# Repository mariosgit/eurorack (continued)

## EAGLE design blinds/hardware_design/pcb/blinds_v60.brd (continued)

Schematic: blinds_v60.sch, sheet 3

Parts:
C31, C34, C35: 47p; C0603
C37, C38: 560p; C0603
IC8, IC9: OPA4171; TSSOP14
IC10: V2164SZ; SOIC16N
J7, J8, J9: PJ301_THONKICONN6; WQP_PJ_301M6
LED5: WP7113SRSGW; LED5MM
LED6: WP937EGW; LED3MM
R61: 205.0k; R0603
R62, R66, R69, R71: 100k; R0603
R63, R76, R78, R79, R89: 100.0k; R0603
R64: 10kB; ALPS_POT_VERTICAL_PS
R65: 10kB; ALPS_POT_VERTICAL
R67, R68, R73: 4.30k; R0603
R70: 3.90k; R0603
R72, R77, R81, R85: 1.0M; R0603
R74, R82: 66.50k; R0603
R75, R80: 1.2k; R0603
R83, R90: 33.20k; R0603
R84: 402; R0603
R87, R88: 510; R0603

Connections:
2_TO_3: R82.2; also elsewhere on the board
3_TO_4: IC8.14 (OUT), R68.1; also elsewhere on the board
AREF_+10: R61.2, R63.1, R79.2; also elsewhere on the board
AREF_-10: R76.2, R89.2; also elsewhere on the board
FOO2: IC10.2 (IN), R88.2, R89.1
GAIN_3: C31.1, IC9.1 (OUT), R66.1, R81.2, R83.2, R90.2
GND: C37.2, C38.2, IC8.3 (+IN), IC8.5 (+IN), IC8.12 (+IN), IC9.3 (+IN), IC9.5 (+IN), IC9.12 (+IN), J7.P1 (1), J8.P1 (1), J9.P1 (1), J9.P2 (2), R64.P$3 (A), R72.2, R75.2, R77.2, R80.2; also elsewhere on the board
unnamed: J8.P3 (3), R84.1
unnamed: C37.1, R87.1
unnamed: IC10.15 (IN), R87.2, R90.1
unnamed: IC8.2 (-IN), IC10.13 (OUT), R67.2
unnamed: C34.1, IC8.6 (-IN), R73.1, R74.2, R82.1, R83.1
unnamed: J9.P3 (3), R71.2
unnamed: IC9.13 (-IN), R65.P$1 (E), R69.2
unnamed: IC9.14 (OUT), R62.2, R69.1
unnamed: C31.2, IC9.2 (-IN), R61.1, R62.1, R64.P$1 (E), R65.P$3 (A), R66.2
unnamed: R64.P$2 (S), R76.1
unnamed: IC9.8 (OUT), LED6.K (C)
unnamed: IC9.9 (-IN), LED6.A, R80.1
unnamed: IC8.8 (OUT), LED5.K (C)
unnamed: IC8.9 (-IN), LED5.A, R75.1
unnamed: IC8.13 (-IN), R68.2, R70.1
unnamed: J8.P2 (2), R70.2
unnamed: IC8.1 (OUT), R67.1, R73.2
unnamed: C38.1, R88.1
unnamed: C35.1, IC9.6 (-IN), IC10.4 (OUT), R78.1, R79.1
unnamed: C35.2, IC9.7 (OUT), IC10.3 (CTRL), IC10.14 (CTRL)
unnamed: R65.P$2 (S), R71.1
unnamed: J7.P3 (3), R78.2
unnamed: J7.P2 (2), R63.2
unnamed: IC8.10 (+IN), R77.1, R85.1
unnamed: IC9.10 (+IN), R72.1, R81.1
OUT3: C34.2, IC8.7 (OUT), R74.1, R84.2, R85.2

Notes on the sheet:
cc-by-sa
Channel 3
Émilie Gillet
emilie.o.gillet@gmail.com

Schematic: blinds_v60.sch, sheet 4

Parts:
C39, C40: 560p; C0603
C44, C45, C48: 47p; C0603
IC10: V2164SZ; SOIC16N
IC11, IC12: OPA4171; TSSOP14
J10, J11, J12: PJ301_THONKICONN6; WQP_PJ_301M6
LED7: WP7113SRSGW; LED5MM
LED8: WP937EGW; LED3MM
R91, R103: 33.20k; R0603
R92, R95, R101, R102, R109: 100.0k; R0603
R93, R94: 510; R0603
R96, R104, R110, R115: 1.0M; R0603
R97: 10kB; ALPS_POT_VERTICAL_PS
R98: 10kB; ALPS_POT_VERTICAL
R99, R100: 4.30k; R0603
R105, R106, R111, R112: 100k; R0603
R107, R114: 66.50k; R0603
R108, R113: 1.2k; R0603
R116: 402; R0603
R117: 205.0k; R0603

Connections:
3_TO_4: R114.2; also elsewhere on the board
AREF_+5: IC11.13 (-IN), IC11.14 (OUT)
AREF_+10: R95.1, R101.2, R117.2; also elsewhere on the board
AREF_-10: R92.2, R109.2; also elsewhere on the board
FOO3: IC10.7 (IN), R92.1, R94.2
GAIN_4: C48.1, IC12.7 (OUT), R91.2, R103.2, R104.2, R112.1
GND: C39.2, C40.2, IC11.3 (+IN), IC11.5 (+IN), IC11.12 (+IN), IC12.3 (+IN), IC12.5 (+IN), IC12.12 (+IN), J10.P1 (1), J11.P1 (1), J12.P1 (1), J12.P2 (2), R96.2, R97.P$3 (A), R108.2, R110.2, R113.2; also elsewhere on the board
unnamed: J10.P3 (3), R102.2
unnamed: J11.P3 (3), R116.1
unnamed: C40.1, R93.1
unnamed: IC10.10 (IN), R91.1, R93.2
unnamed: IC10.12 (OUT), IC11.2 (-IN), R100.2
unnamed: C45.1, IC11.6 (-IN), R99.1, R103.1, R107.2, R114.1
unnamed: J12.P3 (3), R106.2
unnamed: IC12.13 (-IN), R98.P$1 (E), R105.2
unnamed: IC12.14 (OUT), R105.1, R111.2
unnamed: C48.2, IC12.6 (-IN), R97.P$1 (E), R98.P$3 (A), R111.1, R112.2, R117.1
unnamed: R97.P$2 (S), R109.1
unnamed: IC12.8 (OUT), LED8.K (C)
unnamed: IC12.9 (-IN), LED8.A, R113.1
unnamed: IC11.8 (OUT), LED7.K (C)
unnamed: IC11.9 (-IN), LED7.A, R108.1
unnamed: IC11.1 (OUT), R99.2, R100.1
unnamed: R98.P$2 (S), R106.1
unnamed: C39.1, R94.1
unnamed: C44.1, IC10.5 (OUT), IC12.2 (-IN), R101.1, R102.1
unnamed: C44.2, IC10.6 (CTRL), IC10.11 (CTRL), IC12.1 (OUT)
unnamed: J10.P2 (2), R95.2
unnamed: IC11.10 (+IN), R110.1, R115.1
unnamed: IC12.10 (+IN), R96.1, R104.1
OUT4: C45.2, IC11.7 (OUT), R107.1, R115.2, R116.2

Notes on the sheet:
cc-by-sa
Channel 4
Émilie Gillet
emilie.o.gillet@gmail.com

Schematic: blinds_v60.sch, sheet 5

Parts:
C1, C2: 22u; PANASONIC_C
C3, C4, C5, C7, C8, C11, C16, C17, C18, C21, C22, C24, C25, C26, C27, C28, C29, C30, C32, C33, C36, C41, C42, C43, C46, C47: 100n; C0603
D1, D2: 1N5819HW; SOD123
IC1, IC2, IC4, IC5, IC8, IC9, IC11, IC12: OPA4171; TSSOP14
IC3, IC10: V2164SZ; SOIC16N
IC6, IC7: LM4040B10; DBZ_R-PDSO-G3
JP1, JP2, JP3, JP4: FIDUCIAL1X2; FIDUCIAL-1X2
JP5: M05X2PTH; AVR_ICSP
L1, L2: WE-CBF_0603; 0603
P1: PTCSMD; PTC-1206
R25, R86: DNP; R0603
R59, R60: 1.2k; R0603

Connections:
AREF_+10: C3.1, C26.1, C28.1, IC6.1 (C), R59.2; also elsewhere on the board
AREF_-10: C27.1, IC7.2 (A), R60.2; also elsewhere on the board
GND: C1.+, C2.-, C3.2, C4.1, C5.2, C7.2, C8.1, C11.2, C16.1, C17.1, C18.2, C21.2, C22.1, C24.2, C25.2, C26.2, C27.2, C28.2, C29.1, C30.2, C32.2, C33.1, C36.2, C41.1, C42.1, C43.2, C46.2, C47.1, D1.C, IC3.8 (GND), IC6.2 (A), IC7.1 (C), IC10.8 (GND), JP5.3, JP5.4, JP5.5, JP5.6, JP5.7, JP5.8; also elsewhere on the board
unnamed: IC3.1 (MODE), R25.2
unnamed: D2.A, JP5.1, JP5.2
unnamed: JP5.9, JP5.10, P1.2
unnamed: L2.2, P1.1
unnamed: D2.C, L1.2
unnamed: IC10.1 (MODE), R86.2
VCC: C2.+, C5.1, C7.1, C11.1, C18.1, C21.1, C24.1, C30.1, C32.1, C36.1, C43.1, C46.1, IC1.4 (V+), IC2.4 (V+), IC3.16 (V+), IC4.4 (V+), IC5.4 (V+), IC8.4 (V+), IC9.4 (V+), IC10.16 (V+), IC11.4 (V+), IC12.4 (V+), L1.1, R25.1, R59.1, R86.1
VEE: C1.-, C4.2, C8.2, C16.2, C17.2, C22.2, C25.1, C29.2, C33.2, C41.2, C42.2, C47.2, D1.A, IC1.11 (V-), IC2.11 (V-), IC3.9 (V-), IC4.11 (V-), IC5.11 (V-), IC8.11 (V-), IC9.11 (V-), IC10.9 (V-), IC11.11 (V-), IC12.11 (V-), L2.1, R60.1

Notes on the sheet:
cc-by-sa
Power supply
1.2mA delivered
0.8mA needed
Émilie Gillet
emilie.o.gillet@gmail.com

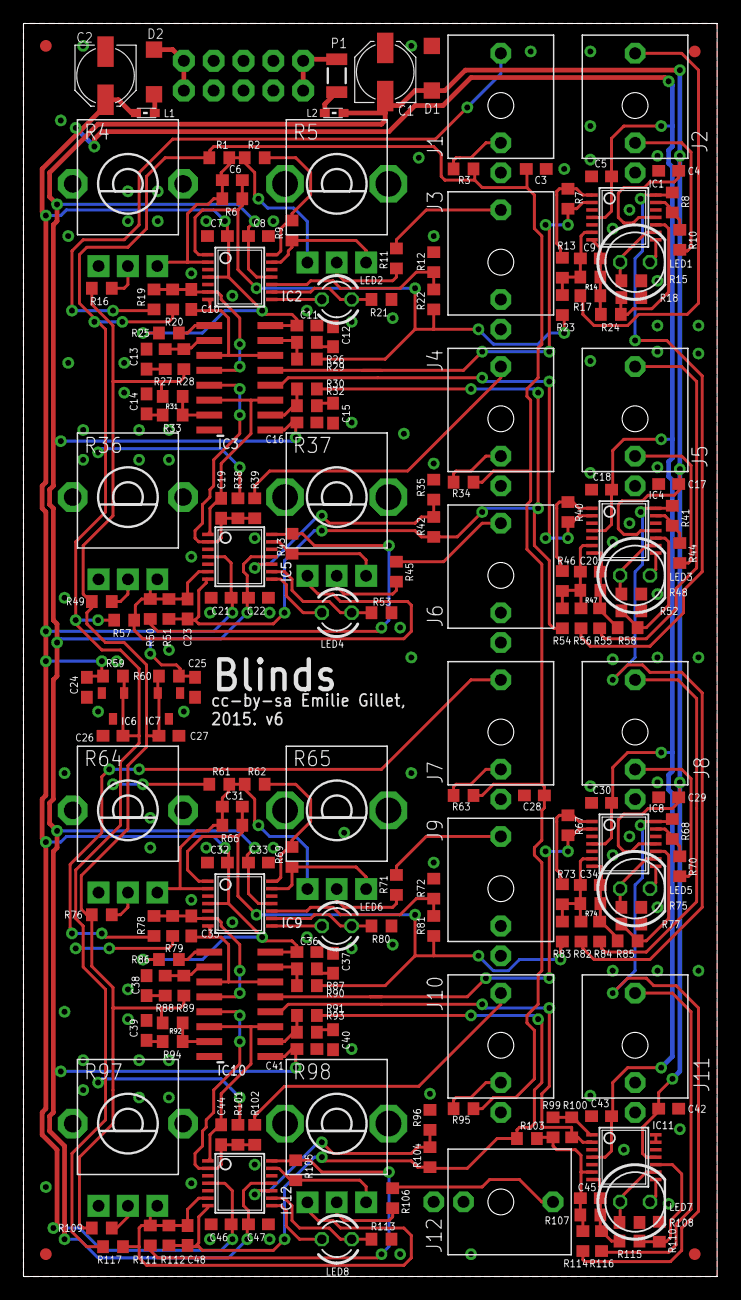
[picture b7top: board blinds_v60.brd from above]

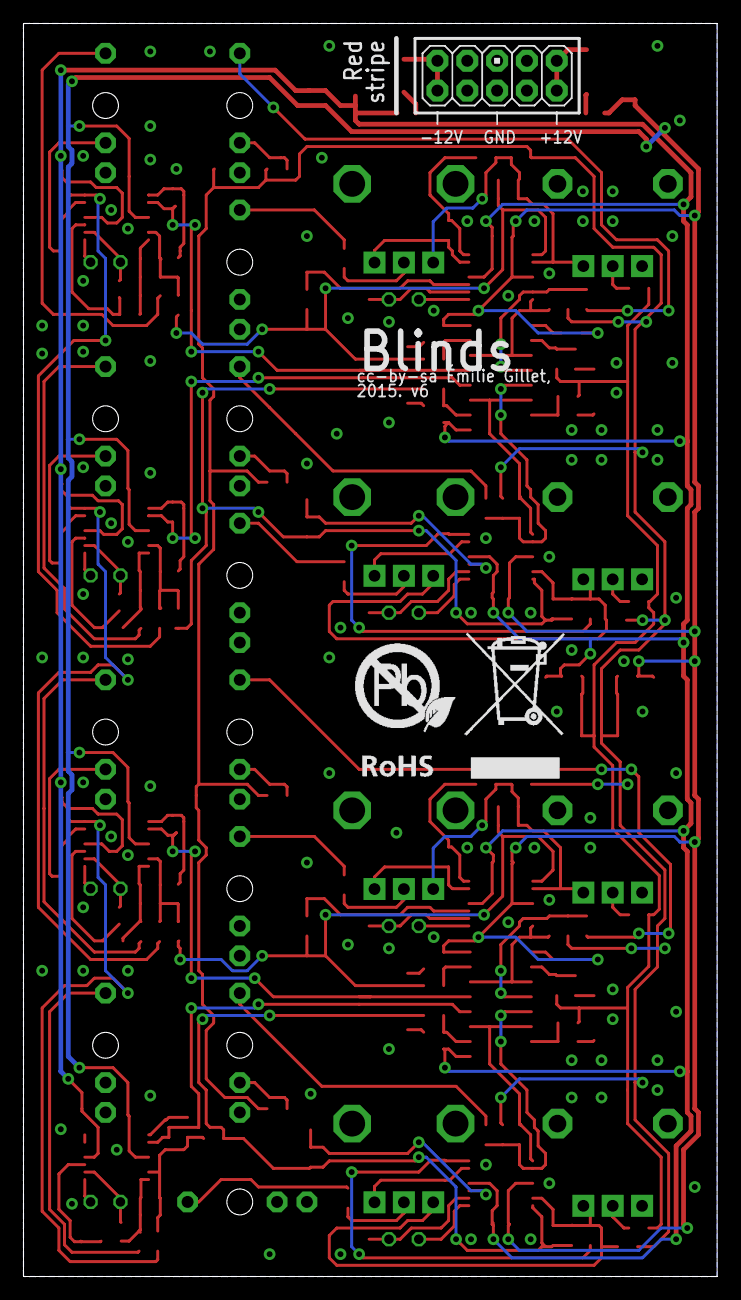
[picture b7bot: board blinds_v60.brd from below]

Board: 2 copper layers, 59.1 x 106.7 mm, 208 parts (2 on the bottom side), 125 nets.

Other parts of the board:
U$2: ROHS_BIG

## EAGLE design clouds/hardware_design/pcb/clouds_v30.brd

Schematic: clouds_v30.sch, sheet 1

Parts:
C6, C7, C47, C48: 18p; C0603
C8, C14, C17, C18, C25, C29, C30, C32, C34: 100n; C0603
C12, C50: 1u; C0603
C19, C24: 2.2u; C0805
C28, C49: 10u; PANASONIC_A
C31, C35: 10u; PANASONIC_B
F1, F2, F3, F4: FIDUCIAL1X2; FIDUCIAL-1X2
IC5: STM32F405RGT6; TQFP-10X10-64
IC8: WM8731; SSOP28
JP1: M06SIP; 1X06
JP2: M05X2MINIJTAG; 2X5-1.27
Q3: 8MHz; HC49UP
Q4: 12.288MHz; HC49UP
R13, R17: 10k; R0603
R40, R41: 2.2k; R0603
SW4, SW5: EVQQ2; EVQ-Q2

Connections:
+3V3: C8.1, C17.1, C18.1, C25.1, C28.+, C29.1, C30.1, C50.1, IC5.19 (VDD_4), IC5.32 (VDD_1), IC5.48 (VDD_2), IC5.64 (VDD_3), IC8.1 (DBVDD), IC8.27 (DCVDD), JP2.1, R17.2, R40.2, R41.2, SW4.B (S), SW4.B' (S1); also elsewhere on the board
+3V3_A: C12.1, C14.1, C31.+, C32.1, C49.+, IC5.13 (VDDA), IC8.8 (HPVDD), IC8.14 (AVDD); also elsewhere on the board
BLEND_CV: IC5.21 (PA5/SPI1_SCK/ADC5/DAC2); also elsewhere on the board
BLEND_POT: IC5.23 (PA7/SPI1_MOSI/ADC7/TIM3_CH2); also elsewhere on the board
BOOT_FLASH: IC5.60 (BOOT0), R13.2, SW4.A, SW4.A' (P1)
DENSITY_CV: IC5.17 (PA3/USART2_RX/ADC3/TIM2_CH4); also elsewhere on the board
GND: C6.1, C7.1, C8.2, C12.2, C14.2, C17.2, C18.2, C19.2, C24.2, C25.2, C28.-, C29.2, C30.2, C31.-, C32.2, C34.2, C35.-, C47.1, C48.1, C49.-, C50.2, IC5.12 (VSSA), IC5.18 (VSS_4), IC5.26 (PB0/ADC8/TIM3_CH3), IC5.28 (PB2/BOOT1), IC5.63 (VSS_3), IC8.11 (HPGND), IC8.15 (AGND), IC8.21 (MODE), IC8.22 (CSB), IC8.28 (DGND), JP1.1, JP2.3, JP2.5, JP2.9, R13.1, SW5.A, SW5.A' (P1); also elsewhere on the board
I2C_SCL: IC5.29 (PB10/SPI2_SCK/I2S_SCK/I2C2_SCL/USART3_TX), IC8.24 (SCLK), R40.1
I2C_SDA: IC5.30 (PB11/I2C2_SDA/USART3_RX), IC8.23 (SDIN), R41.1
I2S_LRCK: IC5.33 (PB12/SPI2_NSS/I2S2_WS/I2C2_SMBA/USART3_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), IC8.5 (DACLRC), IC8.7 (ADCLRC)
I2S_SCK: IC5.34 (PB13/SPI2_SCK/I2S2_SCK/USART3_CTS/TIM1_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), IC8.3 (BCLK)
I2S_SIN: IC5.35 (PB14/SPI2_MISO/USART3_RTS/TIM1_CH2N), IC8.6 (ADCDAT)
I2S_SOUT: IC5.36 (PB15/SPI2_MOSI/I2S2_SD/TIM1_CH3N), IC8.4 (DACDAT)
JTCK: IC5.49 (PA14/JTCK-SWCLK), JP2.4
JTDI: IC5.50 (PA15/JTDI/SPI3_NSS/I2S3_WS), JP2.8
JTDO: IC5.55 (PB3/JTDO/SPI3_SCK/I2S3_SCK), JP2.6
JTMS: IC5.46 (PA13/JTMS-SWDAT), JP2.2
LED_DATA: IC5.57 (PB5/I2C1_SMBA/SPI1_MOSI/SPI3_MOSI/I2S3_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); also elsewhere on the board
LED_EN: IC5.24 (PC4/ADC14); also elsewhere on the board
LED_REC: IC5.62 (PB9/SPI2_NSS/I2S2_WS/I2C1_SDA/TIM4_CH4); also elsewhere on the board
LED_SCK: IC5.25 (PC5/ADC15); also elsewhere on the board
LIN: IC8.20 (LLINEIN); also elsewhere on the board
LOUT: IC8.12 (LOUT); also elsewhere on the board
unnamed: C7.2, IC5.5 (PD0/OSC_IN), Q3.2
unnamed: C6.2, IC5.6 (PD1/OSC_OUT), Q3.1
unnamed: C19.1, IC5.47 (VCAP_2)
unnamed: C34.1, C35.+, IC8.16 (VMID)
unnamed: C24.1, IC5.31 (VCAP_1)
unnamed: C47.2, IC8.26 (XTO), Q4.1
unnamed: C48.2, IC8.25 (XTI/MCLK), Q4.2
PITCH_POT: IC5.9 (PC1/ADC11); also elsewhere on the board
PLAY: IC5.58 (PB6/I2C1_SCL/TIM4_CH1/USART1_TX); also elsewhere on the board
POSITION_POT_CV: IC5.16 (PA2/USART2_TX/ADC2/TIM2_CH3); also elsewhere on the board
REC: IC5.59 (PB7/I2C1_SDA/TIM4_CH2/USART1_RX); also elsewhere on the board
RESET: IC5.7 (NRST), JP2.10, R17.1, SW5.B (S), SW5.B' (S1)
RIN: IC8.19 (RLINEIN); also elsewhere on the board
ROUT: IC8.13 (ROUT); also elsewhere on the board
RX: IC5.43 (PA10/USART1_RX/TIM1_CH3), JP1.4
SIZE_CV: IC5.15 (PA1/USART2_RTS/UART4_RX/ADC1/TIM2_CH2); also elsewhere on the board
SIZE_POT: IC5.8 (PC0/ADC10); also elsewhere on the board
SW_LOAD: IC5.51 (PC10/SPI3_SCK/I2S3_SCK/UART4_TX); also elsewhere on the board
SW_MODE: IC5.52 (PC11/UART4_RX/SPI3_MISO/USART3_RX); also elsewhere on the board
SW_REC: IC5.61 (PB8/TIM4_CH3/I2C1_SCL); also elsewhere on the board
TEXTURE_CV: IC5.14 (PA0-WKUP/USART2_CTS/UART4_TX/ADC0/TIM2_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); also elsewhere on the board
TEXTURE_POT: IC5.22 (PA6/SPI1_MISO/ADC6/TIM3_CH1); also elsewhere on the board
TX: IC5.42 (PA9/USART1_TX/TIM1_CH2), JP1.5
VBAT: IC5.1 (VBAT)
V_OCT: IC5.20 (PA4/SPI1_NSS/SPI3_NSS/USART2_CK/I2S3_WS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); also elsewhere on the board

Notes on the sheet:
cc-by-sa
Main processor
Serial / System Bootloader
grounded if v3.0 or higher
Émilie Gillet
emilie.o.gillet@gmail.com

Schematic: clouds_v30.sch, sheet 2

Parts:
C9, C10, C11, C20, C21, C22: 1n; C0603
C15, C23, C38, C39, C45, C46: 100n; C0603
C33, C36, C37, C41: 10u; PANASONIC_B
C40, C42: 18p; C0603
C43, C44: 220p; C0603
IC3: MCP6002; SO08
IC4: MCP6004; SO14
IC9, IC10: TL072D; SO08
J3, J4, J5, J6, J7, J8, J9, J10, J11, J12: PJ301_THONKICONN6; WQP_PJ_301M6
R18, R43: 10kB; ALPS_POT_VERTICAL_PS
R21, R24, R29, R32, R38, R39: 100k; R0603
R22, R23, R28, R33, R37: 200k; R0603
R25, R26, R35: 33k; R0603
R27, R31: 66.5k; R0603
R34: 47k; R0603
R36: 180k; R0603
R42: PTV112-4420A-A503; BOURNS_PTV112
R46, R47: 3.3k; R0603
R48, R49, R50, R59: 39k; R0603
R51, R52, R53, R54, R55, R56: 5.6k; R0603
R57, R58: 22k; R0603
R61, R62: 1.0k; R0603

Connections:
+3V3_A: C15.1, C23.1, IC3.8 (V+), IC4.4 (V+); also elsewhere on the board
AREF_-10: R18.P$3 (A), R22.2, R23.2, R36.2, R37.2, R43.P$3 (A); also elsewhere on the board
BLEND_CV: C21.2, IC4.7 (OUT), R35.1; also elsewhere on the board
DENSITY_CV: C22.2, IC3.1 (OUT), R31.1; also elsewhere on the board
GND: C15.2, C23.2, C38.2, C39.2, C43.2, C44.2, C45.1, C46.1, IC3.3 (+IN), IC3.4 (V-), IC3.5 (+IN), IC4.3 (+IN), IC4.5 (+IN), IC4.10 (+IN), IC4.11 (V-), IC4.12 (+IN), IC9.3 (+IN), IC9.5 (+IN), IC10.3 (+IN), IC10.5 (+IN), J3.P1 (1), J4.P1 (1), J5.P1 (1), J6.P1 (1), J7.P1 (1), J8.P1 (1), J9.P1 (1), J10.P1 (1), J11.P1 (1), J12.P1 (1), R18.P$1 (E), R43.P$1 (E), R50.1, R54.1, R56.1, R59.1; also elsewhere on the board
LIN: C37.+; also elsewhere on the board
LOUT: C33.+; also elsewhere on the board
LOUT_JACK: J11.P3 (3), R61.1
unnamed: J4.P3 (3), R21.2
unnamed: C10.1, IC4.13 (-IN), R21.1, R22.1, R25.2
unnamed: J10.P3 (3), R24.2
unnamed: C11.1, IC4.9 (-IN), R23.1, R24.1, R26.2
unnamed: J6.P3 (3), R39.2
unnamed: J5.P3 (3), R38.2
unnamed: C20.1, IC4.2 (-IN), R34.2, R36.1, R38.1
unnamed: J9.P3 (3), R32.2
unnamed: C21.1, IC4.6 (-IN), R35.2, R37.1, R39.1
unnamed: C37.-, C44.1, R55.1, R56.2
unnamed: J8.P3 (3), R58.2
unnamed: J7.P3 (3), J8.P2 (2), R57.2
unnamed: C36.-, C43.1, R53.1, R54.2
unnamed: C41.-, R50.2, R52.2
unnamed: C22.1, IC3.2 (-IN), R31.2, R32.1, R33.1
unnamed: C42.1, IC10.6 (-IN), R48.2, R52.1
unnamed: R33.2, R43.P$2 (S)
unnamed: J3.P3 (3), R29.2
unnamed: C42.2, IC10.7 (OUT), R48.1, R62.2
unnamed: C9.1, IC3.6 (-IN), R27.2, R28.1, R29.1
unnamed: C33.-, R51.2, R59.2
unnamed: C40.1, IC10.2 (-IN), R49.2, R51.1
unnamed: C40.2, IC10.1 (OUT), R49.1, R61.2
unnamed: R18.P$2 (S), R28.2
unnamed: IC9.7 (OUT), R42.2P (S), R42.3P (E), R53.2
unnamed: IC9.1 (OUT), R42.2 (S), R42.3 (E), R55.2
unnamed: R42.1P (A), R47.1
unnamed: R42.1 (A), R46.1
unnamed: IC9.6 (-IN), R47.2, R58.1
unnamed: IC9.2 (-IN), R46.2, R57.1
POSITION_POT_CV: C9.2, IC3.7 (OUT), R27.1; also elsewhere on the board
RIN: C36.+; also elsewhere on the board
ROUT: C41.+; also elsewhere on the board
ROUT_JACK: J12.P3 (3), R62.1
SIZE_CV: C10.2, IC4.14 (OUT), R25.1; also elsewhere on the board
TEXTURE_CV: C11.2, IC4.8 (OUT), R26.1; also elsewhere on the board
VCC: C38.1, C39.1, IC9.8 (V+), IC10.8 (V+); also elsewhere on the board
VEE: C45.2, C46.2, IC9.4 (V-), IC10.4 (V-); also elsewhere on the board
V_OCT: C20.2, IC4.1 (OUT), R34.1; also elsewhere on the board

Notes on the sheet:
cc-by-sa
Audio and CV I/O
0.0 to 5.0
-1.5 to 5.5
-5.0 to 5.0
Émilie Gillet
emilie.o.gillet@gmail.com

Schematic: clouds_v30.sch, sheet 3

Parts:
C5: 100n; C0603
IC1: 74HC595D; SO16
J1, J2: PJ301_THONKICONN6; WQP_PJ_301M6
LED1, LED2, LED3, LED4: WP59EGW; LED-BICOLOR-THROUGHHOLE-5MM
Q1, Q2: MMBT3904; SOT23-BEC
R1, R2, R3, R4, R5, R6, R7, R8, R9, R10: 68; R0603
R12, R15: 100k; R0603
R14, R16: 10k; R0603
R19, R20, R44, R45: 10kB; ALPS_POT_VERTICAL_PS
SW1: LP4OA1PBCT
SW2, SW3: TAC_SWITCHPTH; TACTILE-PTH

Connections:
+3V3: C5.1, IC1.10 (SCL), IC1.16 (VCC), R14.2, R16.2; also elsewhere on the board
+3V3_A: R19.P$1 (E), R20.P$1 (E), R44.P$1 (E), R45.P$1 (E); also elsewhere on the board
BLEND_POT: R45.P$2 (S); also elsewhere on the board
GND: C5.2, IC1.8 (GND), IC1.13 (G), J1.P1 (1), J1.P2 (2), J2.P1 (1), J2.P2 (2), LED1.2 (C), LED2.2 (C), LED3.2 (C), LED4.2 (C), Q1.E, Q2.E, R19.P$3 (A), R20.P$3 (A), R44.P$3 (A), R45.P$3 (A), SW1.L2, SW1.P3 (A3), SW1.P6 (B3), SW2.1, SW2.2, SW3.1, SW3.2; also elsewhere on the board
LED_DATA: IC1.14 (SER); also elsewhere on the board
LED_EN: IC1.12 (RCK); also elsewhere on the board
LED_REC: R1.1, R2.1; also elsewhere on the board
LED_SCK: IC1.11 (SCK); also elsewhere on the board
unnamed: LED4.3 (GRN), R9.1
unnamed: LED4.1 (RED), R10.1
unnamed: LED3.1 (RED), R8.1
unnamed: LED3.3 (GRN), R7.1
unnamed: LED2.1 (RED), R6.1
unnamed: J2.P3 (3), R15.1
unnamed: Q2.B, R15.2
unnamed: R1.2, R2.2, SW1.L1
unnamed: LED2.3 (GRN), R5.1
unnamed: LED1.1 (RED), R3.1
unnamed: LED1.3 (GRN), R4.1
unnamed: IC1.15 (QA), R10.2
unnamed: IC1.1 (QB), R9.2
unnamed: IC1.2 (QC), R8.2
unnamed: IC1.3 (QD), R7.2
unnamed: IC1.4 (QE), R6.2
unnamed: IC1.5 (QF), R5.2
unnamed: IC1.6 (QG), R3.2
unnamed: IC1.7 (QH), R4.2
unnamed: J1.P3 (3), R12.1
unnamed: Q1.B, R12.2
PITCH_POT: R20.P$2 (S); also elsewhere on the board
PLAY: Q2.C, R16.1; also elsewhere on the board
REC: Q1.C, R14.1; also elsewhere on the board
SIZE_POT: R19.P$2 (S); also elsewhere on the board
SW_LOAD: SW3.3, SW3.4; also elsewhere on the board
SW_MODE: SW2.3, SW2.4; also elsewhere on the board
SW_REC: SW1.P2 (A2), SW1.P5 (B2); also elsewhere on the board
TEXTURE_POT: R44.P$2 (S); also elsewhere on the board

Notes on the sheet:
cc-by-sa
User interface
Émilie Gillet
emilie.o.gillet@gmail.com

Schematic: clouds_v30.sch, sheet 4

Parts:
C1, C2, C4, C13, C27: 47u; PANASONIC_D
C3, C16, C26: 100n; C0603
D1, D2: 1N5819HW; SOD123
IC2: LM1117-3.3; TO252
IC6: LM4040B10; DBZ_R-PDSO-G3
IC7: LM1117-3.3; SOT223
JP3: M05X2PTH; AVR_ICSP
R11: 4.7; R1206
R30: 470; R0603

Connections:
+3V3: C3.1, C4.+, IC2.3 (VOUT); also elsewhere on the board
+3V3_A: C26.1, C27.+, IC7.2 (VOUT); also elsewhere on the board
AREF_-10: C16.1, IC6.2 (A), R30.2; also elsewhere on the board
GND: C1.-, C2.-, C3.2, C4.-, C13.+, C16.2, C26.2, C27.-, IC2.1 (GND), IC6.1 (C), IC7.1 (GND), JP3.3, JP3.4, JP3.5, JP3.6, JP3.7, JP3.8; also elsewhere on the board
unnamed: C2.+, IC2.2 (VIN), R11.2
unnamed: D1.A, JP3.1, JP3.2
unnamed: D2.C, JP3.9, JP3.10
VCC: C1.+, D1.C, IC7.3 (VIN), R11.1; also elsewhere on the board
VEE: C13.-, D2.A, R30.1; also elsewhere on the board

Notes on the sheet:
1mA
cc-by-sa
Supply
Émilie Gillet
emilie.o.gillet@gmail.com

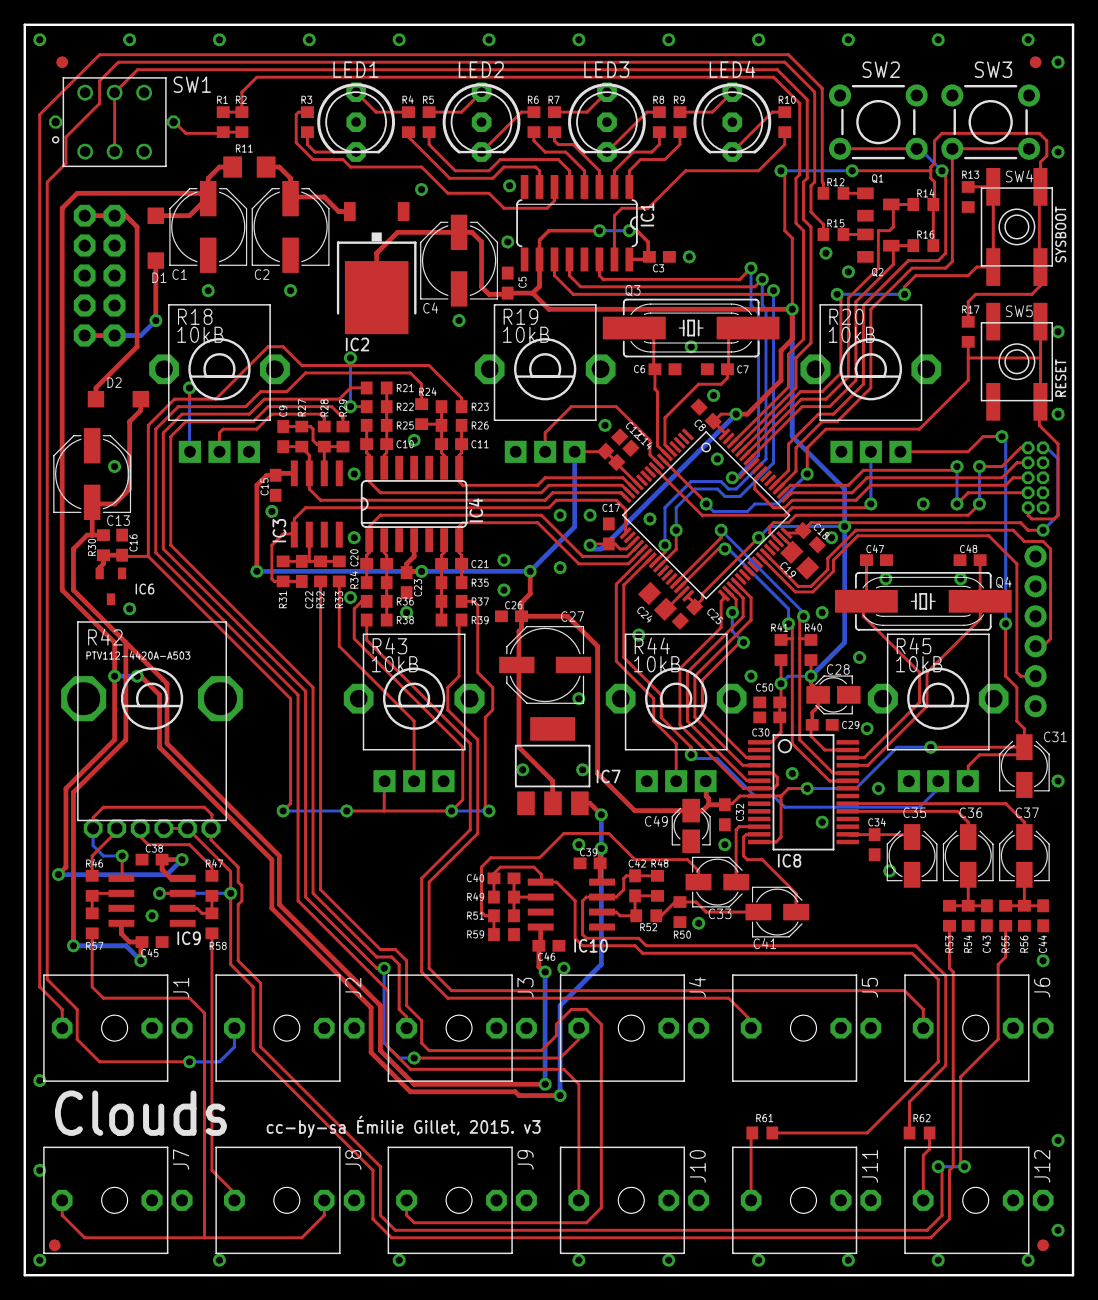
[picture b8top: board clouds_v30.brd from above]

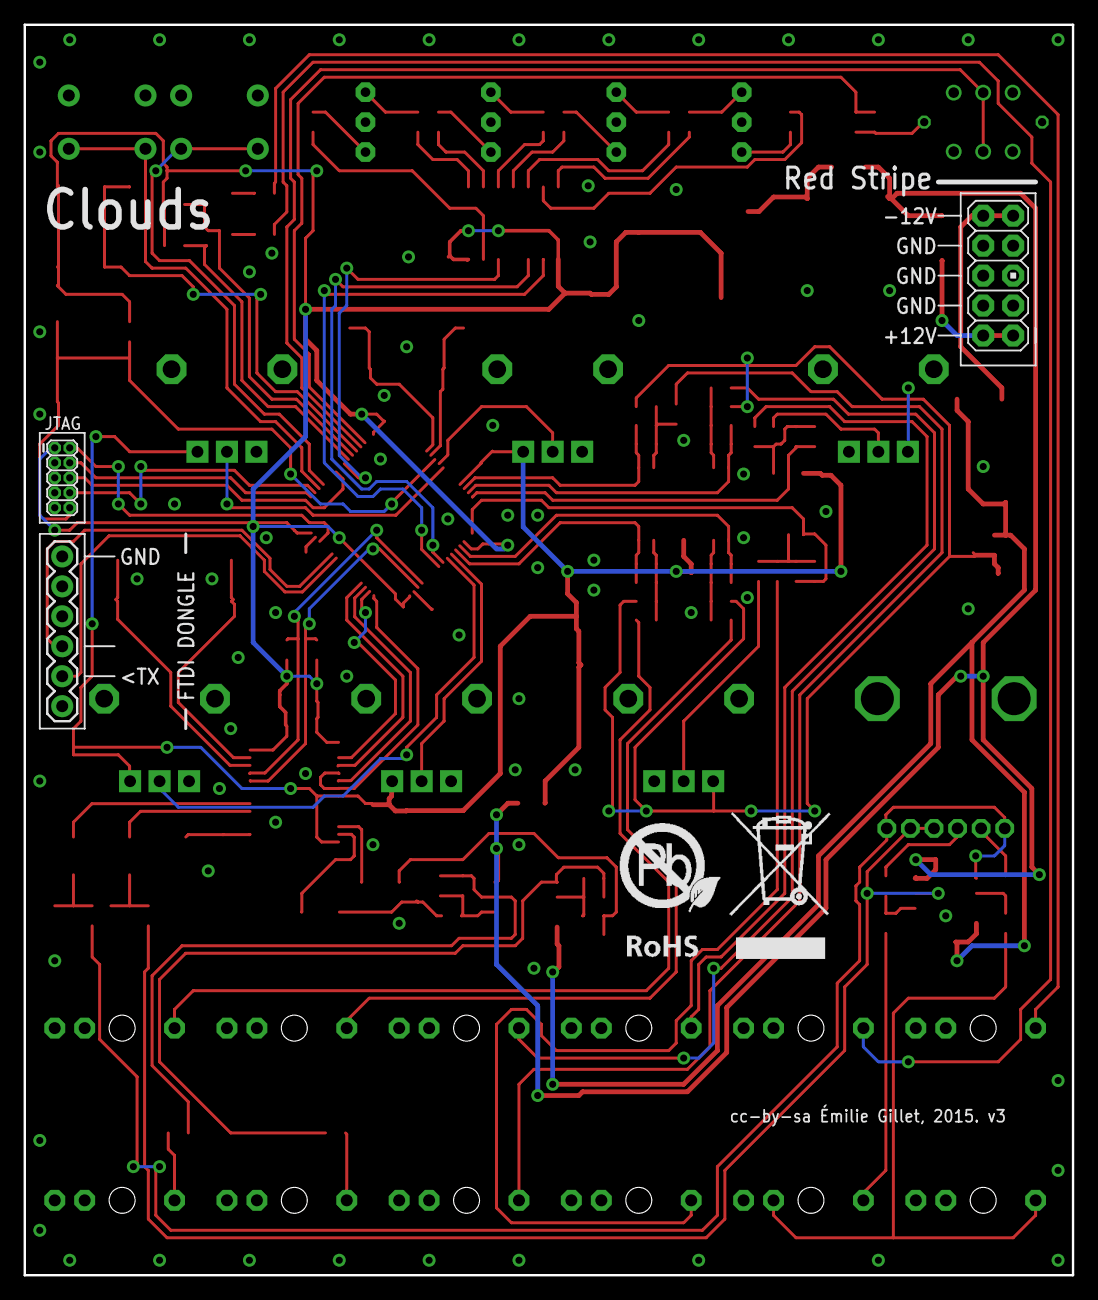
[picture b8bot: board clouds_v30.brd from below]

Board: 2 copper layers, 88.9 x 106.0 mm, 156 parts (4 on the bottom side), 106 nets.

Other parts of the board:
U$2: ROHS_BIG

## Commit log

2020-01-28 grids: changed Plug PM301 footprint, Switch enhanced to Multimec 3FTH9, added parts for MIDI in (not testet)
2020-01-28 stages: changed Poti-LED resistor values from 15k to 150
2020-01-28 howto build reminder for myself
2020-02-04 converting mini packages to 603
2020-02-06 converting mini packages to 603, all done, CRC check ok.
2020-02-15 more build reminders
2020-02-17 updated Plaits BOM with 0603 parts
2020-02-17 marbles -> 0603 pcb done
2020-03-13 marbles bom 603 update
2020-03-13 using older arm c++ 4.8.3 (elements had problems with audio timing)
2020-04-29 Minor stuff..
2020-04-29 Documented my changes.
2020-06-28 Added some signal text, this one works.
2020-06-28 Fixed Collision of c28 with POT, tested ok.
2023-03-20 All PCBs converted to v6, making it KiCad-readable.
2023-04-04 KiCadified branches,shelves,streams.
2023-04-05 Added submodul for kicad libs
2023-04-05 ..shelves kicad..
2023-04-05 tides2 kicadified
2023-05-04 edges->kicad
2023-05-04 refined edges kicad
2023-05-08 Edges pcb optimzed a little
2023-05-09 cleaned up blades dir
2023-05-09 Blades prod info xlsx's
2023-05-09 preped shelves kicad
2023-05-16 Added build instructions for WSL/Docker on Windows
2024-11-14 braids kicad version
2024-11-14 minor
2024-12-07 Blades rprodrun and some more kicad conversion
